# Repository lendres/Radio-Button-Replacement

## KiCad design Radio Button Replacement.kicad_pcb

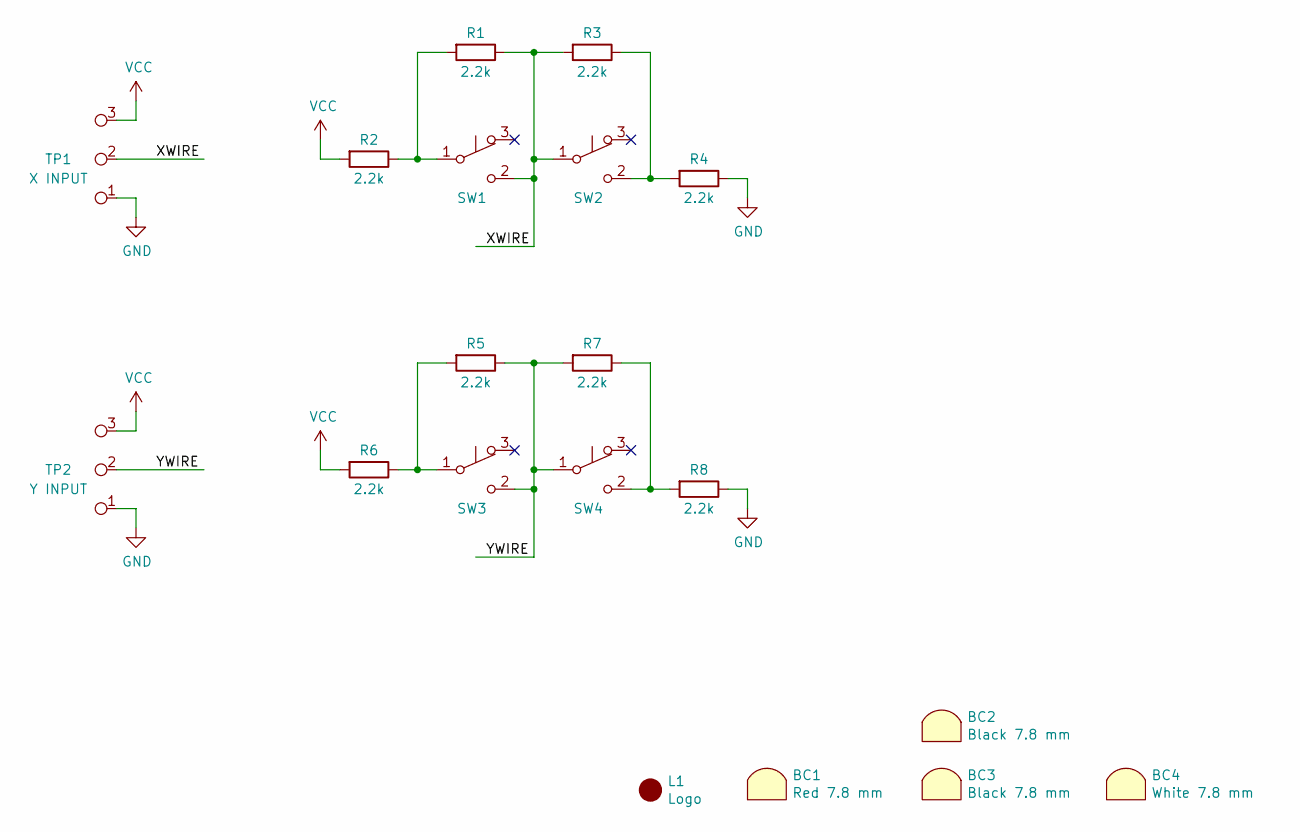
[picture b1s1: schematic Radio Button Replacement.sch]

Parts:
BC1: Red 7.8 mm; ButtonCap; Manufacturer Part No. 801803000
BC2, BC3: Black 7.8 mm; ButtonCap; Manufacturer Part No. 801802000
BC4: White 7.8 mm; ButtonCap; Manufacturer Part No. 801801000
L1: Logo; OSHW-Logo2_7.3x6mm_SilkScreen; Manufacturer Part No. None
R1, R2, R3, R4, R5, R6, R7, R8: 2.2k; R_Axial_DIN0204_L3.6mm_D1.6mm_P7.62mm_Horizontal; Manufacturer Part No. RNMF14FTC2K20
SW1, SW2, SW3, SW4: SW_Push_SPDT_1_3_2; 8125SHZ; Manufacturer Part No. 8125SHZBE
TP1, TP2: TestPoint_3; Pad_3_3.0-5.0; Manufacturer Part No. None

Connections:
/XWIRE: R1.1, R3.2, SW1.2 (NO), SW2.1 (C), TP1.2
/YWIRE: R5.1, R7.2, SW3.2 (NO), SW4.1 (C), TP2.2
GND: R4.1, R8.1, TP1.1, TP2.1
unnamed: R1.2, R2.1, SW1.1 (C)
unnamed: R3.1, R4.2, SW2.2 (NO)
unnamed: R5.2, R6.1, SW3.1 (C)
unnamed: R7.1, R8.2, SW4.2 (NO)
VBUS: R2.2, R6.2, TP1.3, TP2.3

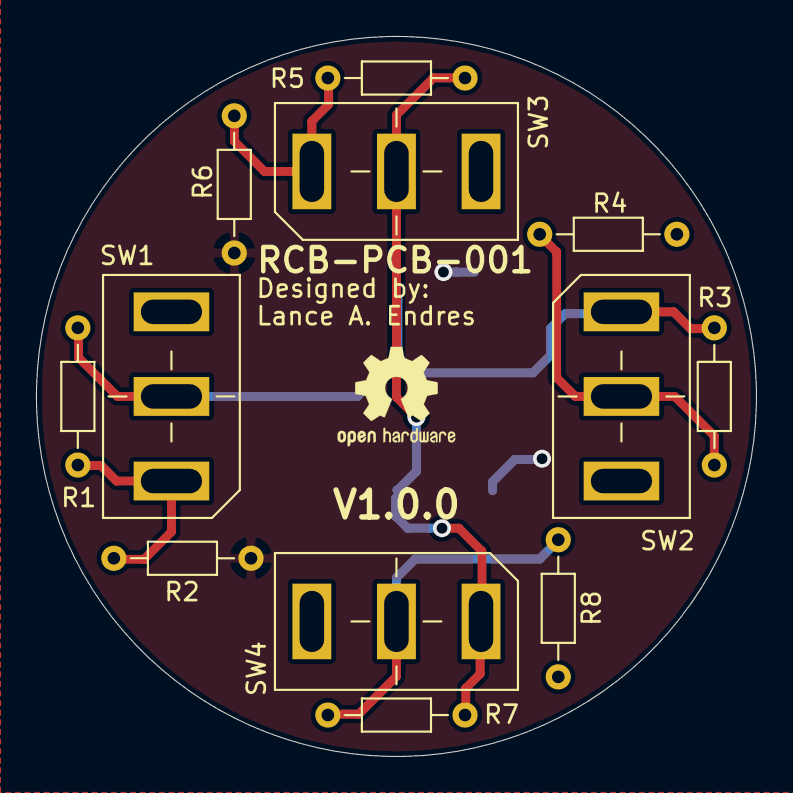
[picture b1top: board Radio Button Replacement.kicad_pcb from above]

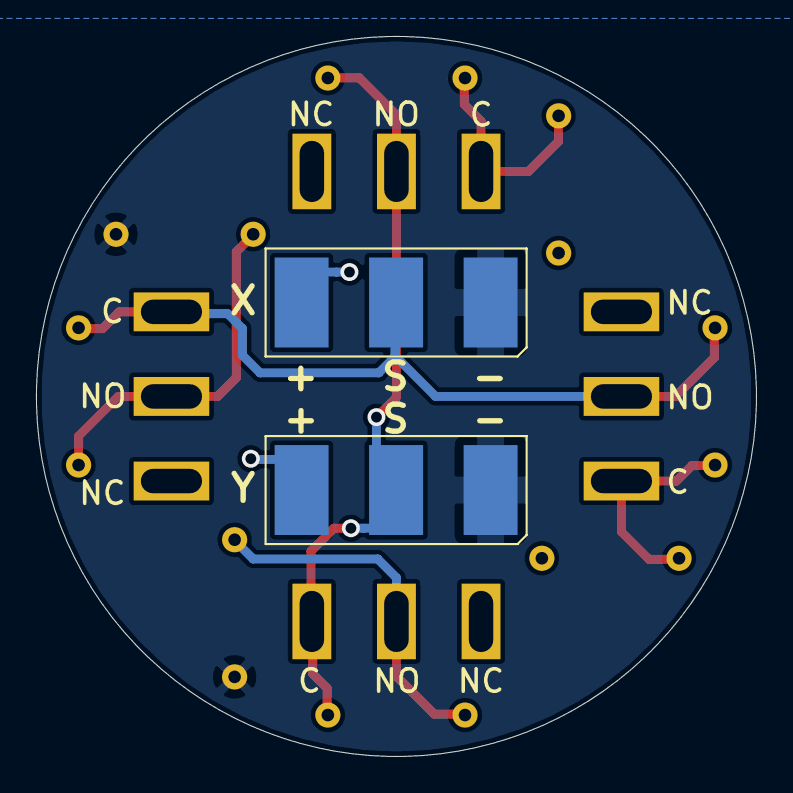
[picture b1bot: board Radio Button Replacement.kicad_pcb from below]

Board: 2 copper layers, 40.0 x 40.0 mm, 19 parts (2 on the bottom side), 8 nets.

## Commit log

2020-08-20 Center marks added
2020-08-22 Update resistor sizes
2020-08-30 Renumbering of components, PCB updates
    Renumbering of components, PCB updates
